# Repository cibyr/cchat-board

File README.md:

This is an **as yet untested** CC1101 board intended for use with [ESPSomfy-RTS](https://github.com/rstrouse/ESPSomfy-RTS), using that project's [recommended pinouts](https://github.com/rstrouse/ESPSomfy-RTS/wiki/Simple-ESPSomfy-RTS-device).

I do not know what I'm doing. Use at your own risk.

Designed in KiCad 6.0.

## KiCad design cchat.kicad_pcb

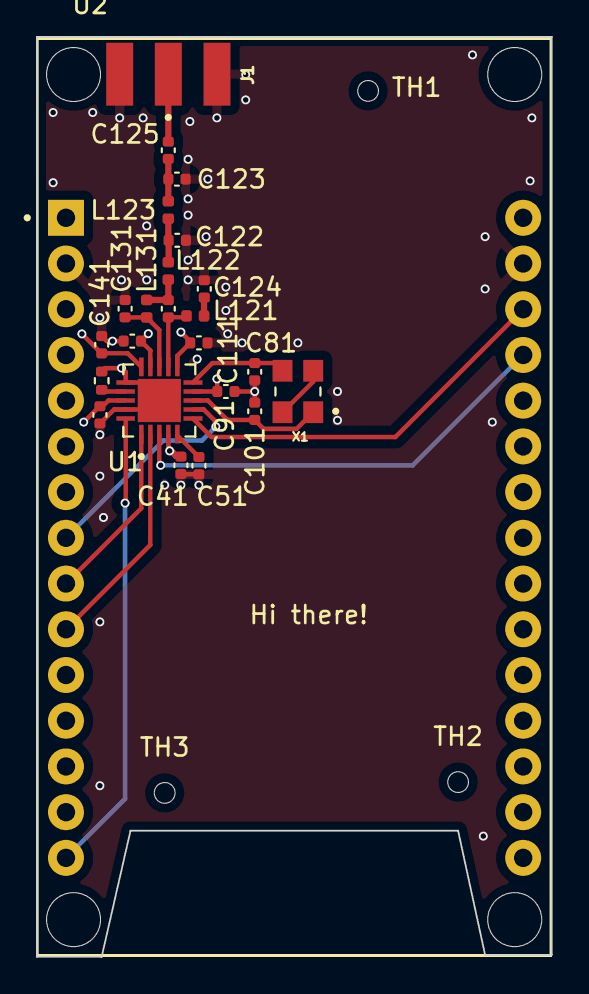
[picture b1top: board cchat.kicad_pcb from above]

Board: 4 copper layers, 28.6 x 51.1 mm, 27 parts (0 on the bottom side), 19 nets.

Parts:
C41, C51: 100 nF; C_0402_1005Metric
C81, C101: 27 pF; C_0402_1005Metric
C91, C141: 10 nF; C_0402_1005Metric
C111, C124, C125, C151, C181: 220 pF; C_0402_1005Metric
C121, C123, C131: 6.8 pF; C_0402_1005Metric
C122: 12 pF; C_0402_1005Metric
J1: CON-SMA-EDGE-S; RFSOLUTIONS_CON-SMA-EDGE-S
L121, L123, L131: 33 nH; L_0402_1005Metric
L122: 18 nH; L_0402_1005Metric
R171: 58 kOhm; R_0402_1005Metric
TH1, TH2, TH3: JLCPCB tooling hole
U1: CC1101RGPR; QFN50P400X400X100-21N
U2: ESP32-DEVKIT-V1; MODULE_ESP32_DEVKIT_V1
X1: NX3225GA-26MHZ-TI; OSCCC320X250X90N

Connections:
/CSN: U1.7 (CSN), U2.8 (D5)
/GDO0: U1.6 (GDO(ATEST)), U2.28 (D13)
/GDO2: U1.3 (GDO2), U2.27 (D12)
/MISO: U1.2 (SO(GDO1)), U2.10 (D19)
/MOSI: U1.20 (SI), U2.15 (D23)
/SCK: U1.1 (SCLK), U2.9 (D18)
GND: C41.2, C51.1, C81.1, C91.2, C101.2, C111.2, C122.2, C123.2, C124.2, C131.1, C141.2, C151.2, C181.2, J1.G1, J1.G2, J1.G3, J1.G4, R171.1, U1.16 (GND_16), U1.19 (GND_19), U1.21 (EXP), U2.2 (GND), U2.29 (GND)
unnamed: C51.2, U1.5 (DCOUPL)
unnamed: C125.2, J1.1
unnamed: C124.1, L121.2
unnamed: C122.1, L122.2, L123.1
unnamed: C123.1, C125.1, L123.2
unnamed: C121.2, L122.1, L131.2
unnamed: C101.1, U1.8 (XOSC_Q1), X1.1
unnamed: C81.2, U1.10 (XOSC_Q2), X1.3
unnamed: C121.1, L121.1, U1.12 (RF_P)
unnamed: C131.2, L131.1, U1.13 (RF_N)
unnamed: R171.2, U1.17 (RBIAS)
VDD: C41.1, C91.1, C111.1, C141.1, C151.1, C181.1, U1.4 (DVDD), U1.9 (AVDD_9), U1.11 (AVDD_11), U1.14 (AVDD_14), U1.15 (AVDD_15), U1.18 (DGUARD), U2.1 (3V3)
